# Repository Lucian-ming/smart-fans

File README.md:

# 智能风扇 Smart Fan

一台能感知环境温度、按需自动调速，并支持**语音、手势、旋钮/按键**控制与 OLED 显示的智能风扇（v1 不联网）。
项目覆盖完整链路：**需求 → 电路设计（KiCad）→ PCB 打样 → 焊接 → 3D 外壳打印 → 固件与上位机开发 → 整机装配与测试**。

> 当前状态：项目骨架已初始化（2026-11-03），选型已确认：**12 V DC 4-pin PWM 风扇 + STM32F103C8T6**，v1 不联网。详见 [需求文档](docs/01-requirements.md)。

## 目录结构

| 路径 | 放什么 | 什么时候用 |
| --- | --- | --- |
| [docs/](docs/) | 需求、架构、路线图、装配/打印说明、实验日志 | 贯穿全程，动手前先看 |
| [hardware/kicad/](hardware/kicad/) | KiCad 原理图 / PCB / 自建库 | 画板、改板、导出生产文件 |
| [hardware/datasheets/](hardware/datasheets/) | 芯片、风扇、传感器的数据手册（PDF） | 选型、查引脚、查电气参数 |
| [hardware/fabrication/](hardware/fabrication/) | 交给板厂的 Gerber / BOM / 坐标文件 | 每次打样固定一份快照 |
| [mechanical/cad/](mechanical/cad/) | 外壳 3D 源文件（FreeCAD / Fusion 等） | 修改结构 |
| [mechanical/step/](mechanical/step/) | 导出给协作方/加工方的 STEP | 与 PCB、风扇做干涉检查 |
| [mechanical/stl/](mechanical/stl/) | 可直接切片打印的 STL | 打印 |
| [mechanical/print-profiles/](mechanical/print-profiles/) | 切片参数（PrusaSlicer / Orca 等） | 复现同一批打印效果 |
| [firmware/](firmware/) | STM32F103 固件（PlatformIO + STM32Cube HAL） | 写代码、烧录、调试 |
| [shared/protocol/](shared/protocol/) | 串口命令协议（v1），固件与工具共用 | 联调前先定协议 |
| [software/](software/) | 串口调试上位机（可选，Python） | 看曲线、批量测试 |
| [references/](references/) | 官方/社区参考例程（语音、手势、OLED、传感器…），不参与编译 | 移植时对照，先跑通再抽片段 |
| [tools/](tools/) | BOM 整理、固件打包、日志分析等脚本 | 减少重复手工操作 |

## 推荐开发顺序

1. **需求与选型** — 定下风扇类型、供电方式、主控、传感器 → `docs/01-requirements.md`
2. **硬件** — 原理图 → PCB → 检查 → 下单打样 → 到货焊接 → 上电测试
3. **机械** — 先打印 1:1 关键件试配合（PCB 定位柱、风扇孔位），再整体打印
4. **软件** — 先打通"温度 → PWM → 风扇转速"最小闭环，再加联网与 App
5. **集成** — 整机装配、老化测试、记录问题 → 迭代下一版

> 硬件与外壳不要并行到"全部完成"再合并：PCB 尺寸一变，外壳就得重画。建议 PCB 定版（至少尺寸与安装孔冻结）后再开外壳。

## 工程约定

- 版本：硬件用 `revA / revB`，每次投板在 `hardware/fabrication/` 建日期快照目录。
- 文件命名：`功能_版本.扩展名`，小写加下划线，如 `fan_ctrl_revA.kicad_pcb`。
- 固件版本：`firmware/platformio.ini` 中的 `FW_VERSION` 宏，烧录后串口打印。
- 每次实验（尤其是失败）追加一条记录到 [docs/logs/](docs/logs/)。

## 已确认选型

| 项目 | 决定 |
| --- | --- |
| 风扇 | 12 V DC 4-pin PWM（12025），PWM 25 kHz + FG 测速 |
| 主控 | STM32F103C8T6（64 KB Flash / 20 KB RAM） |
| 传感器 | DS18B20 单总线 |
| 交互 | 旋转编码器 + 0.96" OLED（I²C）+ 蜂鸣器 |
| 语音 | SU-03T / ASR-PRO 离线语音模块（UART2，词条在厂商平台配置） |
| 手势 | PAJ7620U2（I²C1，与 OLED 共用总线） |
| 联网 | v1 不做，仅 UART1 调试 |

详见 [需求文档](docs/01-requirements.md) 与 [引脚分配](docs/hardware/pinmap.md)。

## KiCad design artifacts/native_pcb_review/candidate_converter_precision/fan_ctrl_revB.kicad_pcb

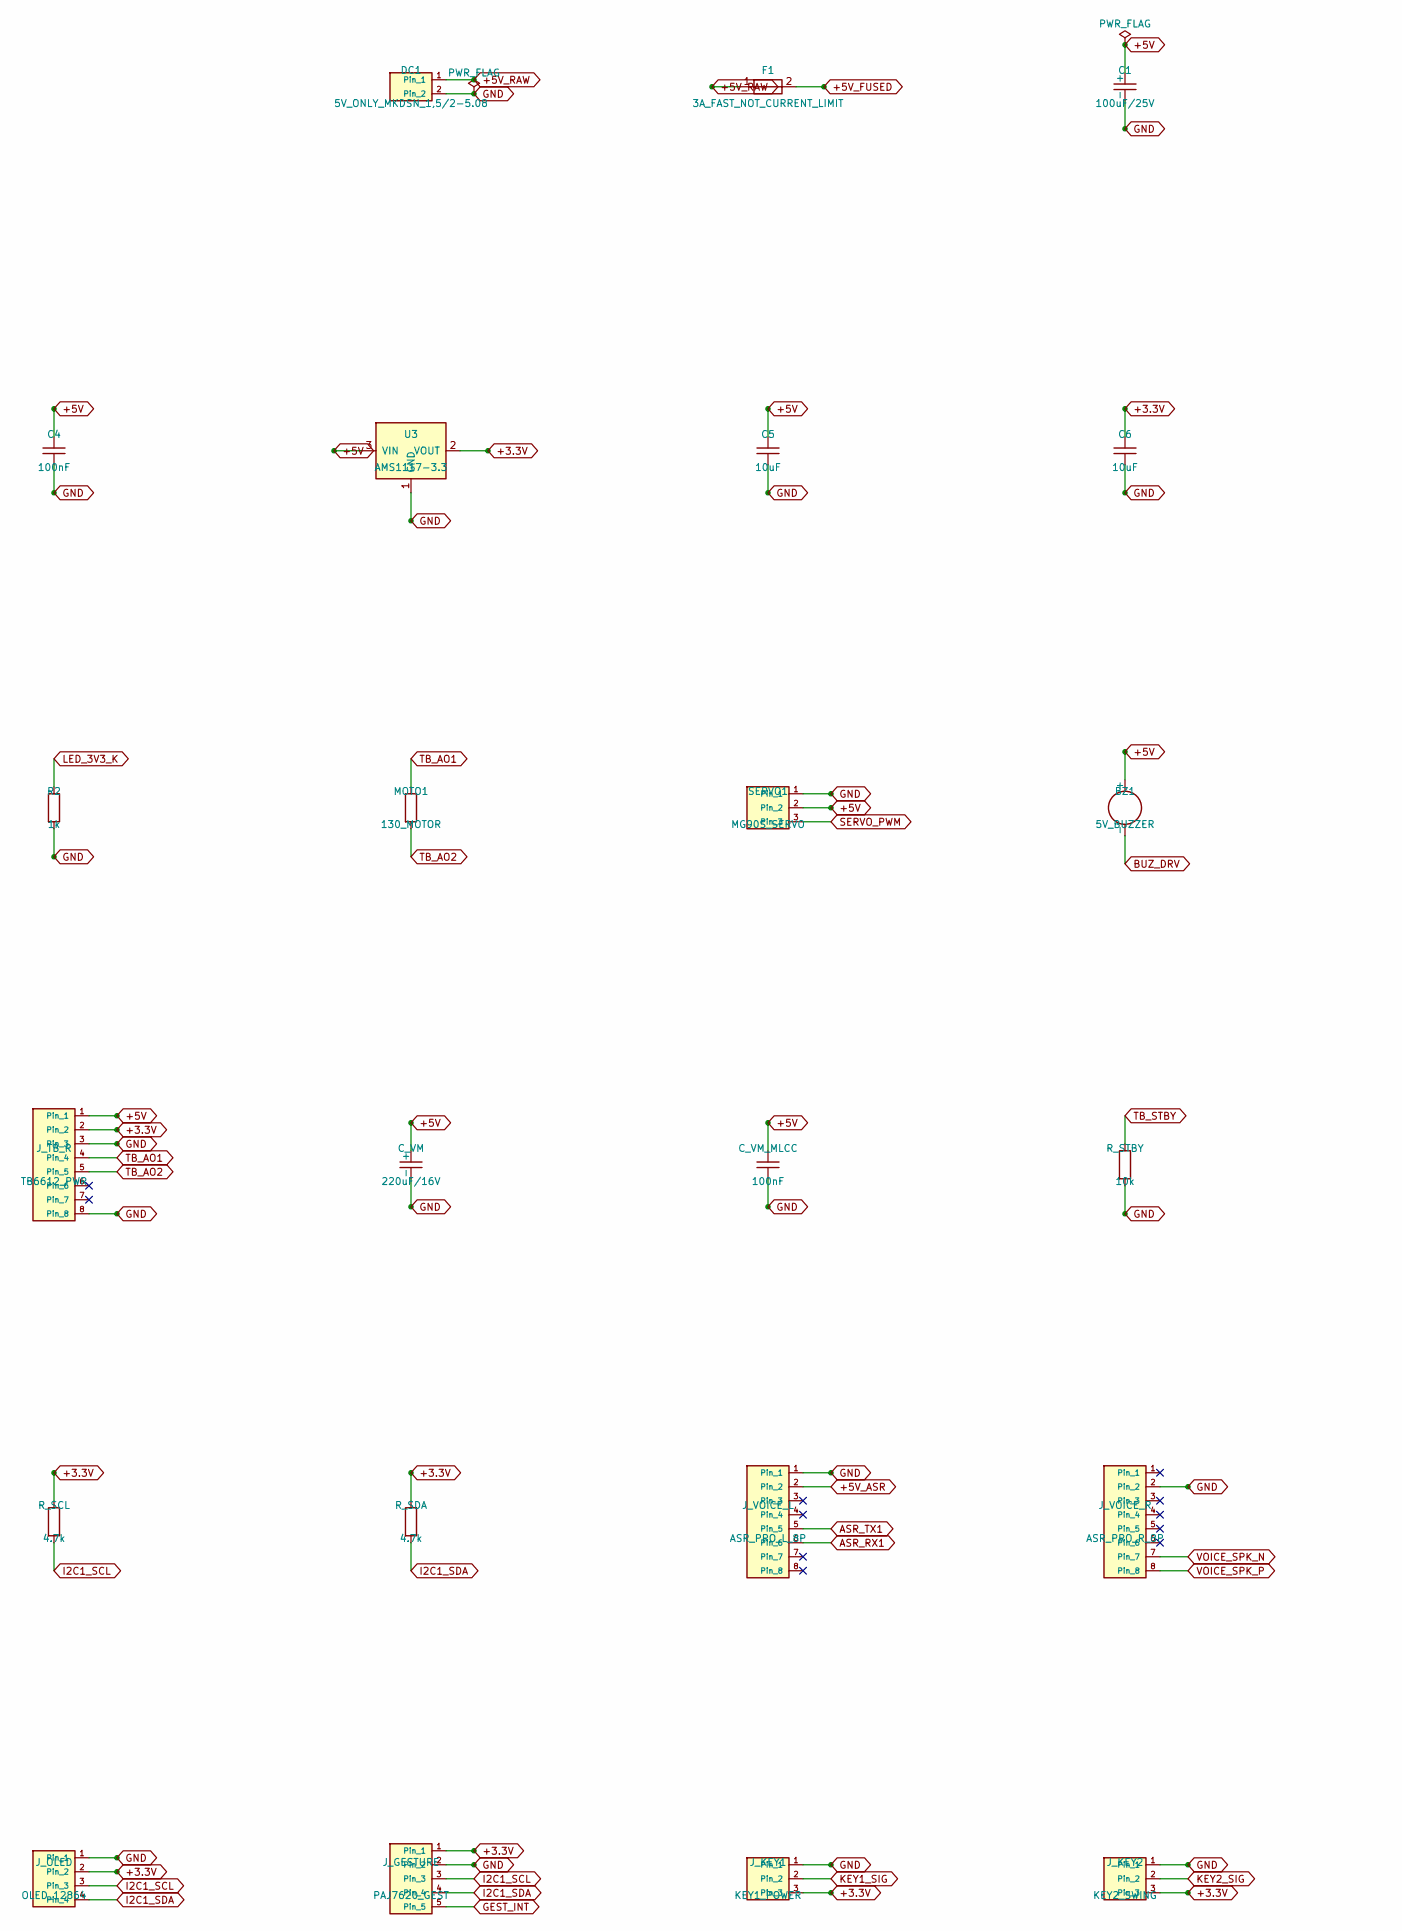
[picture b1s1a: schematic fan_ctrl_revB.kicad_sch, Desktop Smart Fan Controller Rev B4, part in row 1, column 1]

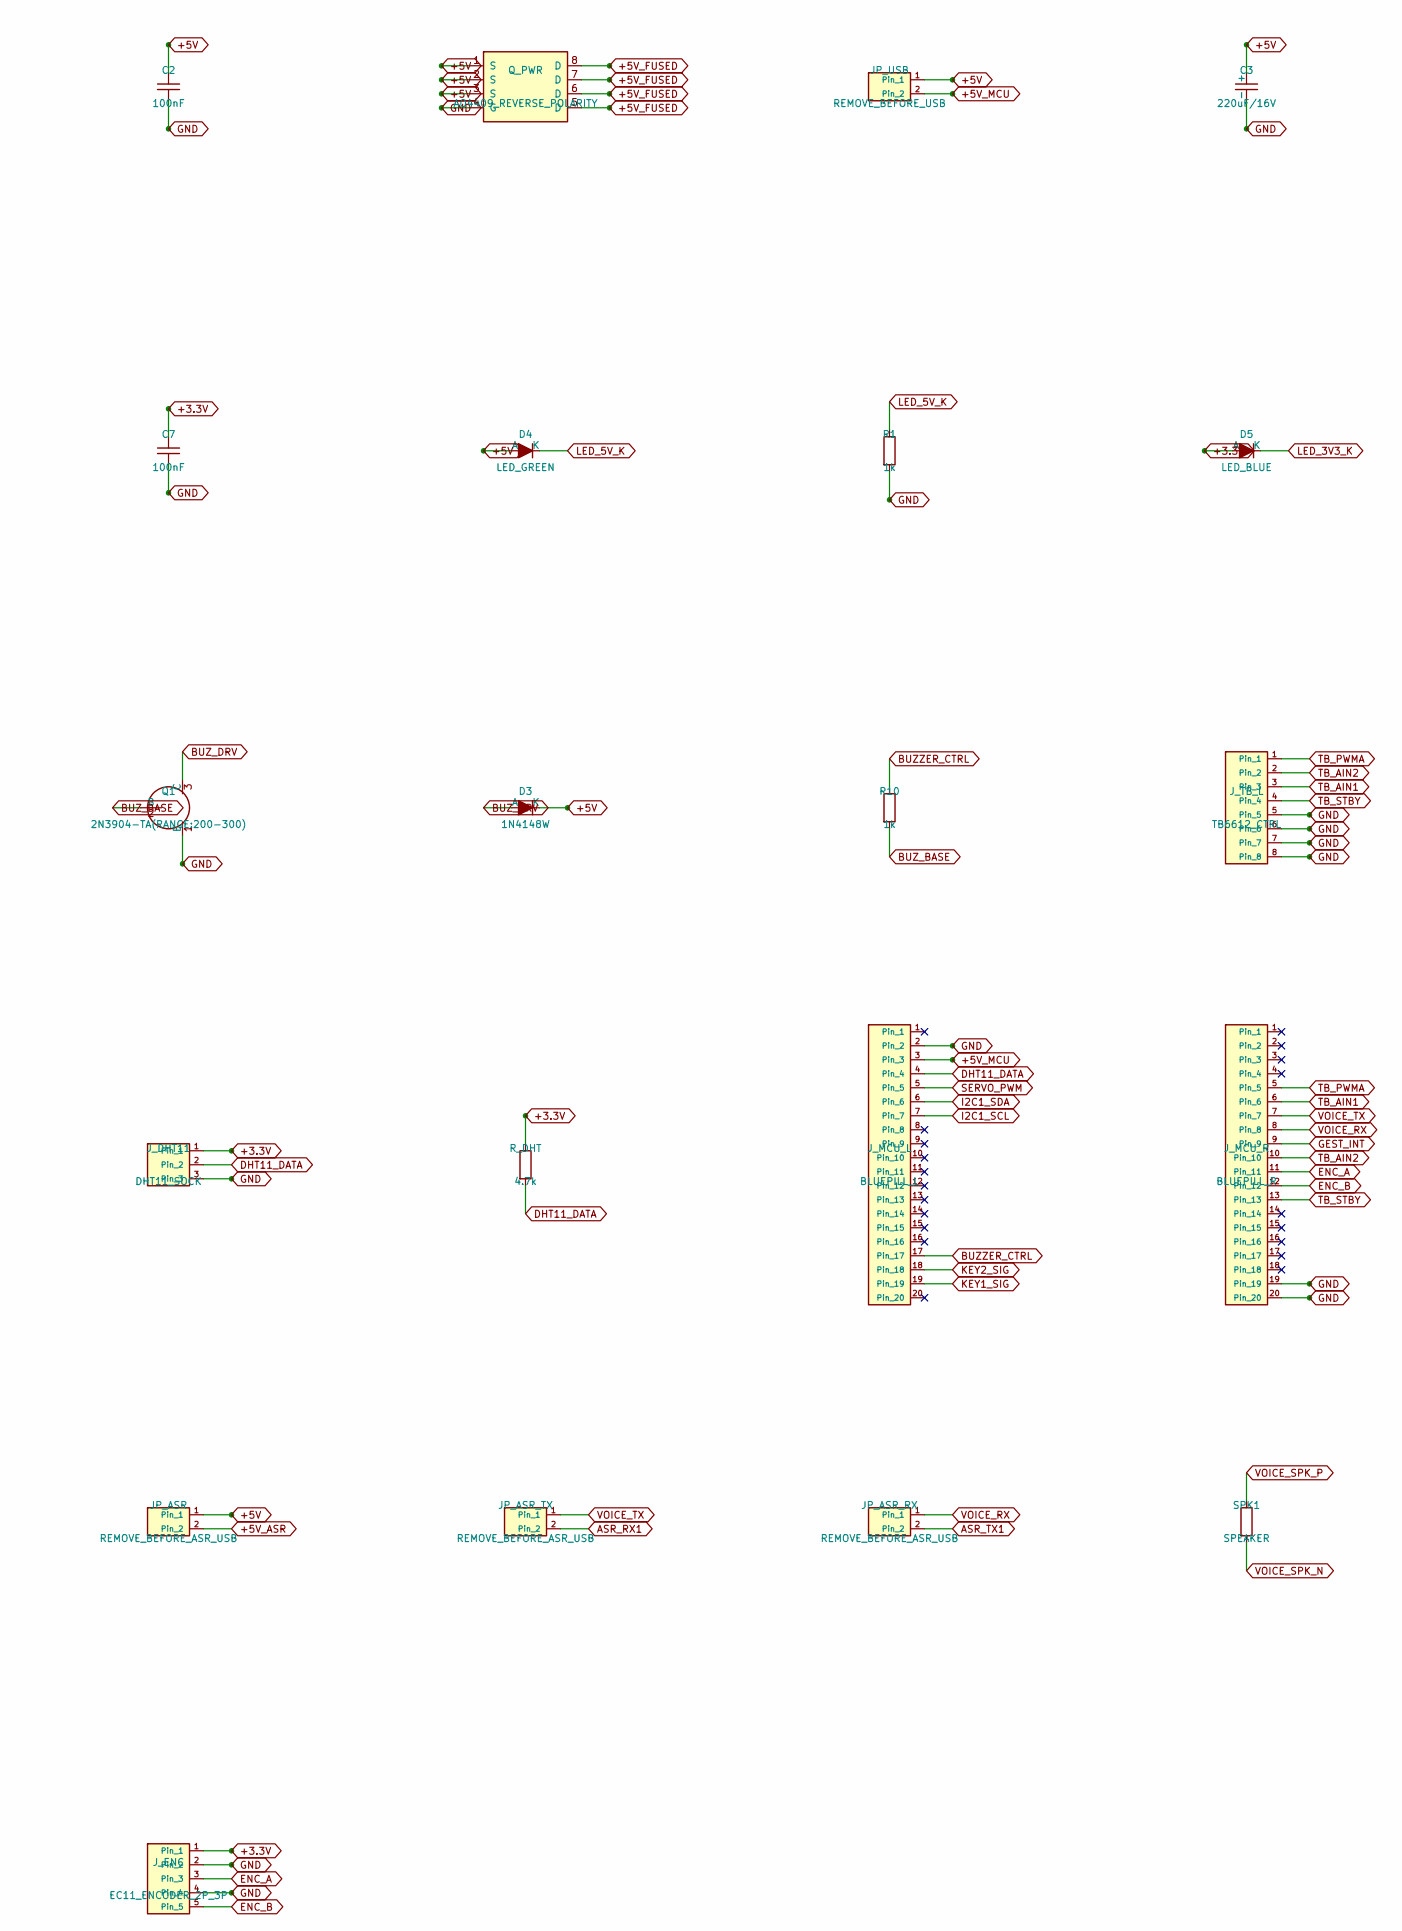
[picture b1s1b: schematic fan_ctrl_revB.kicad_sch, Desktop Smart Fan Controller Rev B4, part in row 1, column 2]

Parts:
BZ1: 5V_BUZZER; Board_BZ1; LCSC C96093
C1: 100uF/25V; Board_C1; LCSC C134665
C2: 100nF; Board_C2; LCSC C49678
C3: 220uF/16V; Board_C3; LCSC C338177
C4: 100nF; Board_C4; LCSC C49678
C5: 10uF; Board_C5; LCSC C15849
C6: 10uF; Board_C6; LCSC C15849
C7: 100nF; Board_C7; LCSC C49678
C_VM: 220uF/16V; Board_C_VM; LCSC C338177
C_VM_MLCC: 100nF; Board_C_VM_MLCC; LCSC C49678
D3: 1N4148W; Board_D3; LCSC C81598
D4: LED_GREEN; Board_D4; LCSC C2292
D5: LED_BLUE; Board_D5; LCSC C2293
DC1: 5V_ONLY_MKDSN_1,5/2-5.08; Board_DC1
F1: 3A_FAST_NOT_CURRENT_LIMIT; Board_F1
JP_ASR: REMOVE_BEFORE_ASR_USB; Board_JP_ASR
JP_ASR_RX: REMOVE_BEFORE_ASR_USB; Board_JP_ASR_RX
JP_ASR_TX: REMOVE_BEFORE_ASR_USB; Board_JP_ASR_TX
JP_USB: REMOVE_BEFORE_USB; Board_JP_USB
J_DHT11: DHT11_SOCK; Board_J_DHT11; LCSC C2718487
J_ENC: EC11_ENCODER_2P_3P; Board_J_ENC
J_GESTURE: PAJ7620_GEST; Board_J_GESTURE; LCSC C50950
J_KEY1: KEY1_POWER; Board_J_KEY1; LCSC C2718487
J_KEY2: KEY2_SWING; Board_J_KEY2; LCSC C2718487
J_MCU_L: BLUEPILL_L; Board_J_MCU_L; LCSC C50984
J_MCU_R: BLUEPILL_R; Board_J_MCU_R; LCSC C50984
J_OLED: OLED_12864; Board_J_OLED; LCSC C2718488
J_TB_L: TB6612_CTRL; Board_J_TB_L; LCSC C27438
J_TB_R: TB6612_PWR; Board_J_TB_R; LCSC C27438
J_VOICE_L: ASR_PRO_L_8P; Board_J_VOICE_L
J_VOICE_R: ASR_PRO_R_8P; Board_J_VOICE_R
MOTO1: 130_MOTOR; Board_MOTO1; LCSC C5258883
Q1: 2N3904-TA(RANGE:200-300); Board_Q1; LCSC C2081
Q_PWR: AO4409_REVERSE_POLARITY; Board_Q_PWR
R1: 1k; Board_R1; LCSC C17513
R2: 1k; Board_R2; LCSC C17513
R10: 1k; Board_R10; LCSC C17513
R_DHT: 4.7k; Board_R_DHT; LCSC C17673
R_SCL: 4.7k; Board_R_SCL; LCSC C17673
R_SDA: 4.7k; Board_R_SDA; LCSC C17673
R_STBY: 10k; Board_R_STBY; LCSC C17414
SERVO1: MG90S_SERVO; Board_SERVO1; LCSC C2718487
SPK1: SPEAKER; Board_SPK1; LCSC C5258883
U3: AMS1117-3.3; Board_U3; LCSC C6186

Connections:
+3.3V: C6.1, C7.1, D5.2 (A), J_DHT11.1, J_ENC.1, J_GESTURE.1, J_KEY1.3, J_KEY2.3, J_OLED.2, J_TB_R.2, R_DHT.1, R_SCL.1, R_SDA.1, U3.2 (VOUT)
+5V: BZ1.1 (+), C1.1 (+), C2.1, C3.1 (+), C4.1, C5.1, C_VM.1 (+), C_VM_MLCC.1, D3.1 (K), D4.2 (A), JP_ASR.1, JP_USB.1, J_TB_R.1, Q_PWR.1 (S), Q_PWR.2 (S), Q_PWR.3 (S), SERVO1.2, U3.3 (VIN)
+5V_ASR: JP_ASR.2, J_VOICE_L.2
+5V_FUSED: F1.2, Q_PWR.5 (D), Q_PWR.6 (D), Q_PWR.7 (D), Q_PWR.8 (D)
+5V_MCU: JP_USB.2, J_MCU_L.3
+5V_RAW: DC1.1, F1.1
ASR_RX1: JP_ASR_TX.2, J_VOICE_L.6
ASR_TX1: JP_ASR_RX.2, J_VOICE_L.5
BUZZER_CTRL: J_MCU_L.17, R10.1
BUZ_BASE: Q1.2 (B), R10.2
BUZ_DRV: BZ1.2 (-), D3.2 (A), Q1.3 (C)
DHT11_DATA: J_DHT11.2, J_MCU_L.4, R_DHT.2
ENC_A: J_ENC.3, J_MCU_R.11
ENC_B: J_ENC.5, J_MCU_R.12
GEST_INT: J_GESTURE.5, J_MCU_R.9
GND: C1.2 (-), C2.2, C3.2 (-), C4.2, C5.2, C6.2, C7.2, C_VM.2 (-), C_VM_MLCC.2, DC1.2, J_DHT11.3, J_ENC.2, J_ENC.4, J_GESTURE.2, J_KEY1.1, J_KEY2.1, J_MCU_L.2, J_MCU_R.19, J_MCU_R.20, J_OLED.1, J_TB_L.5, J_TB_L.6, J_TB_L.7, J_TB_L.8, J_TB_R.3, J_TB_R.8, J_VOICE_L.1, J_VOICE_R.2, Q1.1 (E), Q_PWR.4 (G), R1.2, R2.2, R_STBY.2, SERVO1.1, U3.1 (GND); also elsewhere on the board
I2C1_SCL: J_GESTURE.3, J_MCU_L.7, J_OLED.3, R_SCL.2
I2C1_SDA: J_GESTURE.4, J_MCU_L.6, J_OLED.4, R_SDA.2
KEY1_SIG: J_KEY1.2, J_MCU_L.19
KEY2_SIG: J_KEY2.2, J_MCU_L.18
LED_3V3_K: D5.1 (K), R2.1
LED_5V_K: D4.1 (K), R1.1
SERVO_PWM: J_MCU_L.5, SERVO1.3
TB_AIN1: J_MCU_R.6, J_TB_L.3
TB_AIN2: J_MCU_R.10, J_TB_L.2
TB_AO1: J_TB_R.4, MOTO1.1
TB_AO2: J_TB_R.5, MOTO1.2
TB_PWMA: J_MCU_R.5, J_TB_L.1
TB_STBY: J_MCU_R.13, J_TB_L.4, R_STBY.1
VOICE_RX: JP_ASR_RX.1, J_MCU_R.8
VOICE_SPK_N: J_VOICE_R.7, SPK1.2
VOICE_SPK_P: J_VOICE_R.8, SPK1.1
VOICE_TX: JP_ASR_TX.1, J_MCU_R.7

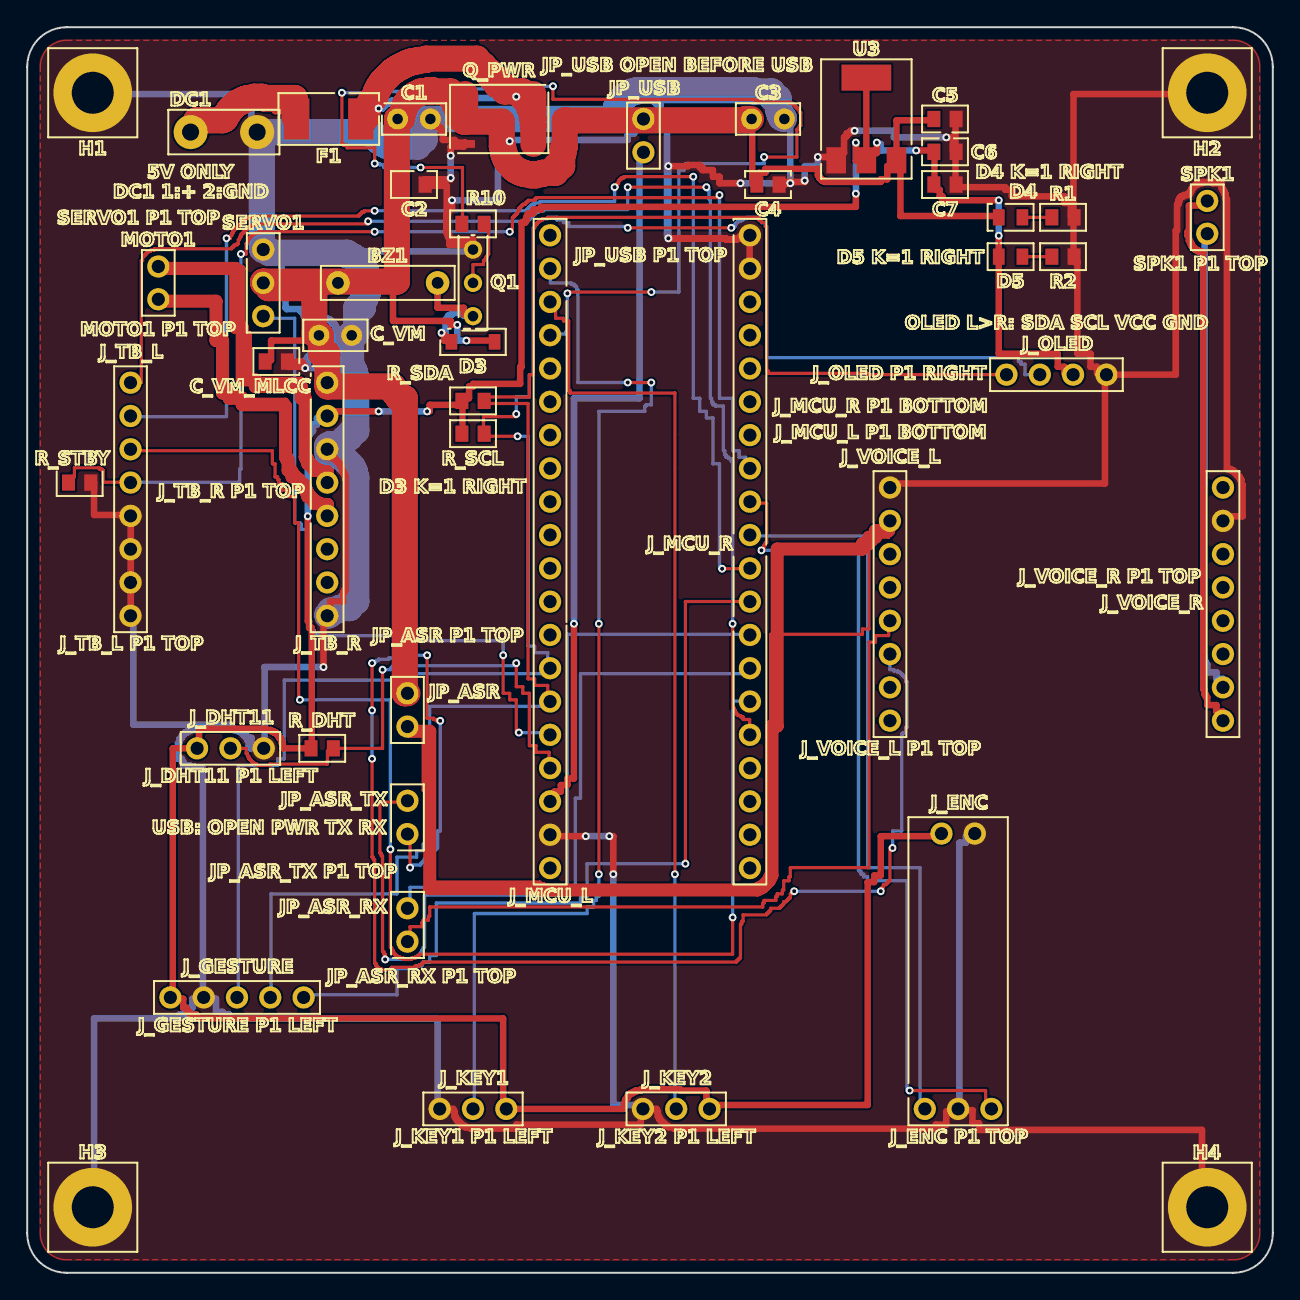
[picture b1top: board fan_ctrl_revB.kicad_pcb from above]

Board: 2 copper layers, 95.0 x 95.0 mm, 48 parts (0 on the bottom side), 33 nets.

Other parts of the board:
H1: MountingHole_M3; Board_H1
H2: MountingHole_M3; Board_H2
H3: MountingHole_M3; Board_H3
H4: MountingHole_M3; Board_H4

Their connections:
GND: H1.1, H2.1, H3.1, H4.1; also elsewhere on the board

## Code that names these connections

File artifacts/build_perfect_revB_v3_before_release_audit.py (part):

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Fixes all defects from the Rev B2 engineering audit:
1. P0-1: Full GND copper plane with real (filled_polygon ...) in .kicad_pcb, G36/G37 in Gerber, and 28 GND stitching vias
2. P0-2: Perfect Blue Pill physical pinout alignment (0 insertion short circuit, verified pin-by-pin against physical board)
3. P0-3: ENC_A and ENC_B assigned to Net 30/31, fully connected to STM32 PA6/PA7
4. P0-4: Generous 95.0 x 95.0 mm board with R3 corners and 85.0 mm hole pitch, zero component collisions (>=1.2mm everywhere)
5. True 25-degree sloped front console on 3D CAD with all 6 openings (OLED, Gesture, 2 Buttons, Encoder, Mic)
6. KiCad schematic with full lib_symbols, wires, junctions, and authentic netlist
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            ("1", 0.0, -24.13, "+3.3V", 1.7, 1.0),      # 3V3
            ("2", 0.0, -21.59, "GND", 1.7, 1.0),        # GND
            ("3", 0.0, -19.05, "+5V", 1.7, 1.0),        # 5V
            ("4", 0.0, -16.51, "DHT11_DATA", 1.7, 1.0), # PB9
            ("5", 0.0, -13.97, "SERVO_PWM", 1.7, 1.0),  # PB8 (TIM4_CH3)
            ("6", 0.0, -11.43, "I2C1_SDA", 1.7, 1.0),   # PB7
            ("7", 0.0, -8.89, "I2C1_SCL", 1.7, 1.0),    # PB6
            ("8", 0.0, -6.35, "NC", 1.7, 1.0),          # PB5
            ("9", 0.0, -3.81, "NC", 1.7, 1.0),          # PB4
            ("10", 0.0, -1.27, "NC", 1.7, 1.0),         # PB3
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            ("14", 0.0, 8.89, "NC", 1.7, 1.0),          # PA10
            ("15", 0.0, 11.43, "NC", 1.7, 1.0),         # PA9
            ("16", 0.0, 13.97, "NC", 1.7, 1.0),         # PA8
            ("17", 0.0, 16.51, "BUZZER_CTRL", 1.7, 1.0),# PB15
            ("18", 0.0, 19.05, "KEY2_SIG", 1.7, 1.0),   # PB14 (Swing/Mode)
            ("19", 0.0, 21.59, "KEY1_SIG", 1.7, 1.0),   # PB13 (Power)
            ("20", 0.0, 24.13, "ENC_SW", 1.7, 1.0)      # PB12 (Encoder center switch)
        ]
    },
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            ("2", 0.0, -21.59, "NC", 1.7, 1.0),         # PC13
            ("3", 0.0, -19.05, "NC", 1.7, 1.0),         # PC14
            ("4", 0.0, -16.51, "NC", 1.7, 1.0),         # PC15
            ("5", 0.0, -13.97, "TB_PWMA", 1.7, 1.0),    # PA0 (TIM2_CH1)
            ("6", 0.0, -11.43, "TB_AIN1", 1.7, 1.0),    # PA1
            ("7", 0.0, -8.89, "VOICE_TX", 1.7, 1.0),    # PA2 (USART2_TX)
            ("8", 0.0, -6.35, "VOICE_RX", 1.7, 1.0),    # PA3 (USART2_RX)
            ("9", 0.0, -3.81, "GEST_INT", 1.7, 1.0),    # PA4 (EXTI4)
            ("10", 0.0, -1.27, "TB_AIN2", 1.7, 1.0),    # PA5
            ("11", 0.0, 1.27, "ENC_A", 1.7, 1.0),       # PA6 (TIM3_CH1)
            ("12", 0.0, 3.81, "ENC_B", 1.7, 1.0),       # PA7 (TIM3_CH2)
            ("13", 0.0, 6.35, "TB_STBY", 1.7, 1.0),     # PB0
            ("14", 0.0, 8.89, "NC", 1.7, 1.0),          # PB1
            ("15", 0.0, 11.43, "NC", 1.7, 1.0),         # PB10
            ("16", 0.0, 13.97, "NC", 1.7, 1.0),         # PB11
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            ("1", -5.08, 0.0, "GND", 1.7, 1.0),
            ("2", -2.54, 0.0, "+3.3V", 1.7, 1.0),
            ("3", 0.0, 0.0, "ENC_SW", 1.7, 1.0),
            ("4", 2.54, 0.0, "ENC_B", 1.7, 1.0),        # Pin 4 is ENC_B (PA7)
            ("5", 5.08, 0.0, "ENC_A", 1.7, 1.0)         # Pin 5 is ENC_A (PA6)
        ]
    },

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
